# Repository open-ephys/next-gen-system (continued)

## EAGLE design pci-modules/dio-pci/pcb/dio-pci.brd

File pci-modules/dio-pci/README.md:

# Intan & DIO FMC Daughter Card

This board roughly conforms the PCIe card mechanical standard and uses a flex
FMC cable to connect to the master FPGA module. This board performs all
communication over FMC -- the PCIe slot design is for mechanical support and to
provide a common and standardized mounting solution across acquisition PCs

This card is part of the overall proposed architecture of the next-gen system
which is outlined
[here](https://open-ephys.atlassian.net/wiki/display/OEW/PCIe+acquisition+board)

### Features
- See TODO item on isolation...
- 2x isolated intan compatible 12pin omnetics connectors (A & B) for the intan headstage SPI standard, isolated through LVDS to CMOS converters and galvanic isolators. This headstage has its own power supply that is fed through am isolated DC-DC converter.
- 4x directional SMA connectors (on the card front edge) that are routed through the same isolation circuit as headstage connectors

### Pinout
FMC LPC pinout can be found [here](https://docs.google.com/spreadsheets/d/18WfmbLGt8bGUUdksKp6AKA_wMX2SJ3Tndin-nnEgUCs/edit#gid=584734392)

### BOM
The bill of materials for this device can be found
[here](https://docs.google.com/spreadsheets/d/18WfmbLGt8bGUUdksKp6AKA_wMX2SJ3Tndin-nnEgUCs/edit?usp=sharing).

## Manufacturing requirements

TODO:
- PCB thickness:
- 4 layers
- 8mil trace width & spacing
- 12mil min. drill

PCI Brackets:
http://www.mouser.com/Search/ProductDetail.aspx?R=9203virtualkey53400000virtualkey534-9203
http://www.cbttechnology.com/products/s/PCI/PCI-blanks-database.php
http://www.keyelco.com/category.cfm/Standard-Blanks/Computer-Bracket-Blanks-With-Tabs/p/427/id/704/c_id/899

There is one 0.05" pitch BGA connector (the samtech FMC connector) and a few omnetics connectors with inacessible pins on the board, so a stencil and reflow soldering need to be used.

The Samtec FMC connector might need to be clamped or held down during reflow soldering. The samtec docs state that they should settle on their own during reflow though, so trying that first seems like a good idea (  http://suddendocs.samtec.com/processing/searay_soldering1.pdf ).

There is a round pad of kapton tape on the connector to provide a clamping surface for this purpose. We have had good success with using a steel paperclip that we modified to exert less force by cutting two slots into the spring. The original paper clips push down too hard and can warp the conenctor. Possibly just weighting it down with a suitable object could also work. Finally, the size of the connector means that it heats up pretty slowly, so expect it to reflow after everything else on the board, and if possible use proper pre-heating.

In order to meet approximately correct trace impedances, the design further is assuming:
 - 1oz copper
 - ~1.2mm total board height, ~0.25mm per layer, dielectric ER = 4.5

## TODO (Rev 1.0)
- [ ] Instead of conforming to VITA 57, PCB footprint should be made to fit in
  a PC expansion slot and be connected to the KC705 using a flex [FMC
  cable](http://suddendocs.samtec.com/prints/hdr-169472-xx-mkt.pdf). This will
  modularize the IO modules, potentially creating an ecosystem of different
  modules for different applications. It will also use extremely standardized
  interface (rear PC expansion slots) which also have excellent
  electrical/mechanical characteristics.
    - A couple interesting IO Module ideas
        - Analog module (e.g. NI DAQ replacement with some beefy multiplex SAR
          ADC and DAC on it)
        - Isolated Intan module (Similar to existing design, featuring galvanic
          isolation)
        - Adjustable logic level digital IO module
        - SPI compression module
        - Etc...
- [ ] As per [page 24 of the KC705 user
  guide](http://www.xilinx.com/support/documentation/boards_and_kits/kc705/ug810_KC705_Eval_Bd.pdf)
  we need to jumper the TDI and TDO pins of our FMC connectors to allow pass
  through of JTAG signals so the FPGA can be programmed when the FMC module is
  connected.
- [ ] For galvanically isolated IO module, we should conform to human use
  standards. Jakob has some info on what is required for this.
- [ ] SMA input jacks should optionally terminate in 50 Ohms via a transistor switch
- [ ] SMA outputs should have 50 ohm characteristic impedance and use line
  drivers capable of reaching TTL logic levels (>2V) when driving 50 Ohm load
- [ ] What does isolation mean in the context of being inside a computer
  chassis? I have a feeling that it does not mean much because the case of the
  computer is tied to earth. Isolation will probably need to happen outside the
  computer case. Perhaps keeping the digital IO isolation in place is a good
  idea to prevent users from destroying things, but power/ground isolation
  inside the computer is probably mute.

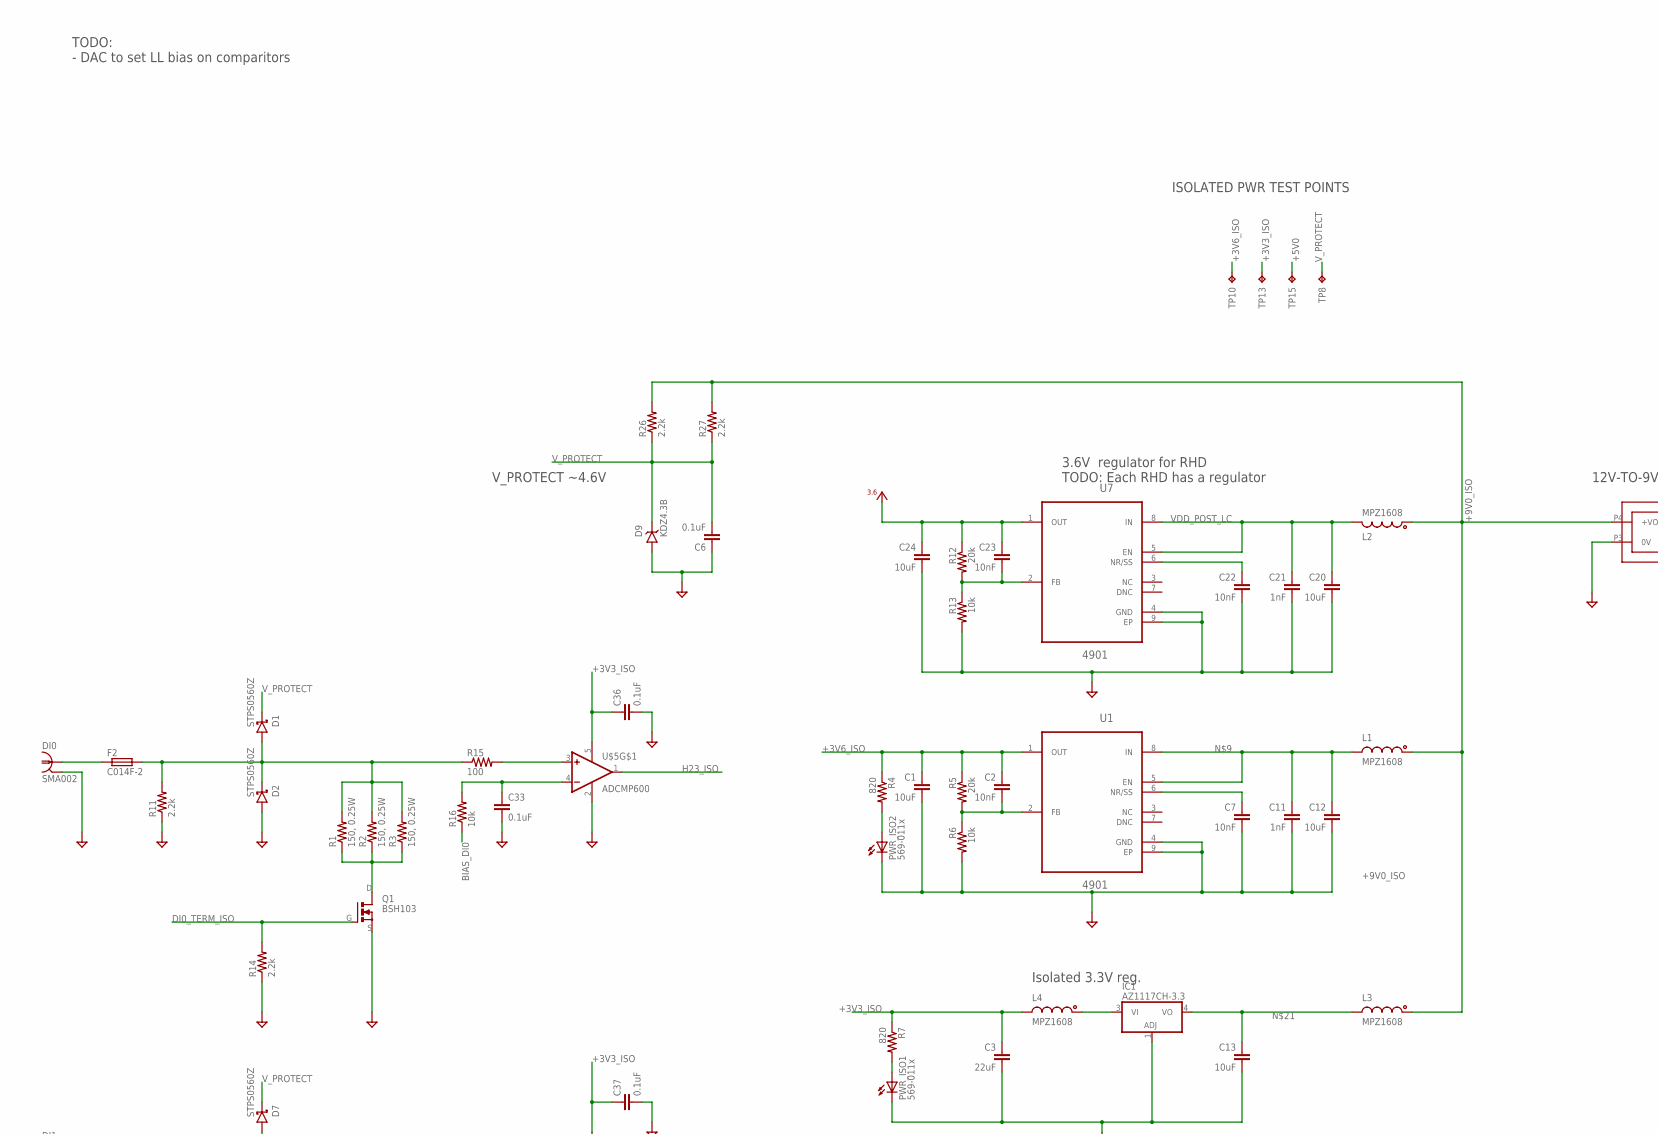
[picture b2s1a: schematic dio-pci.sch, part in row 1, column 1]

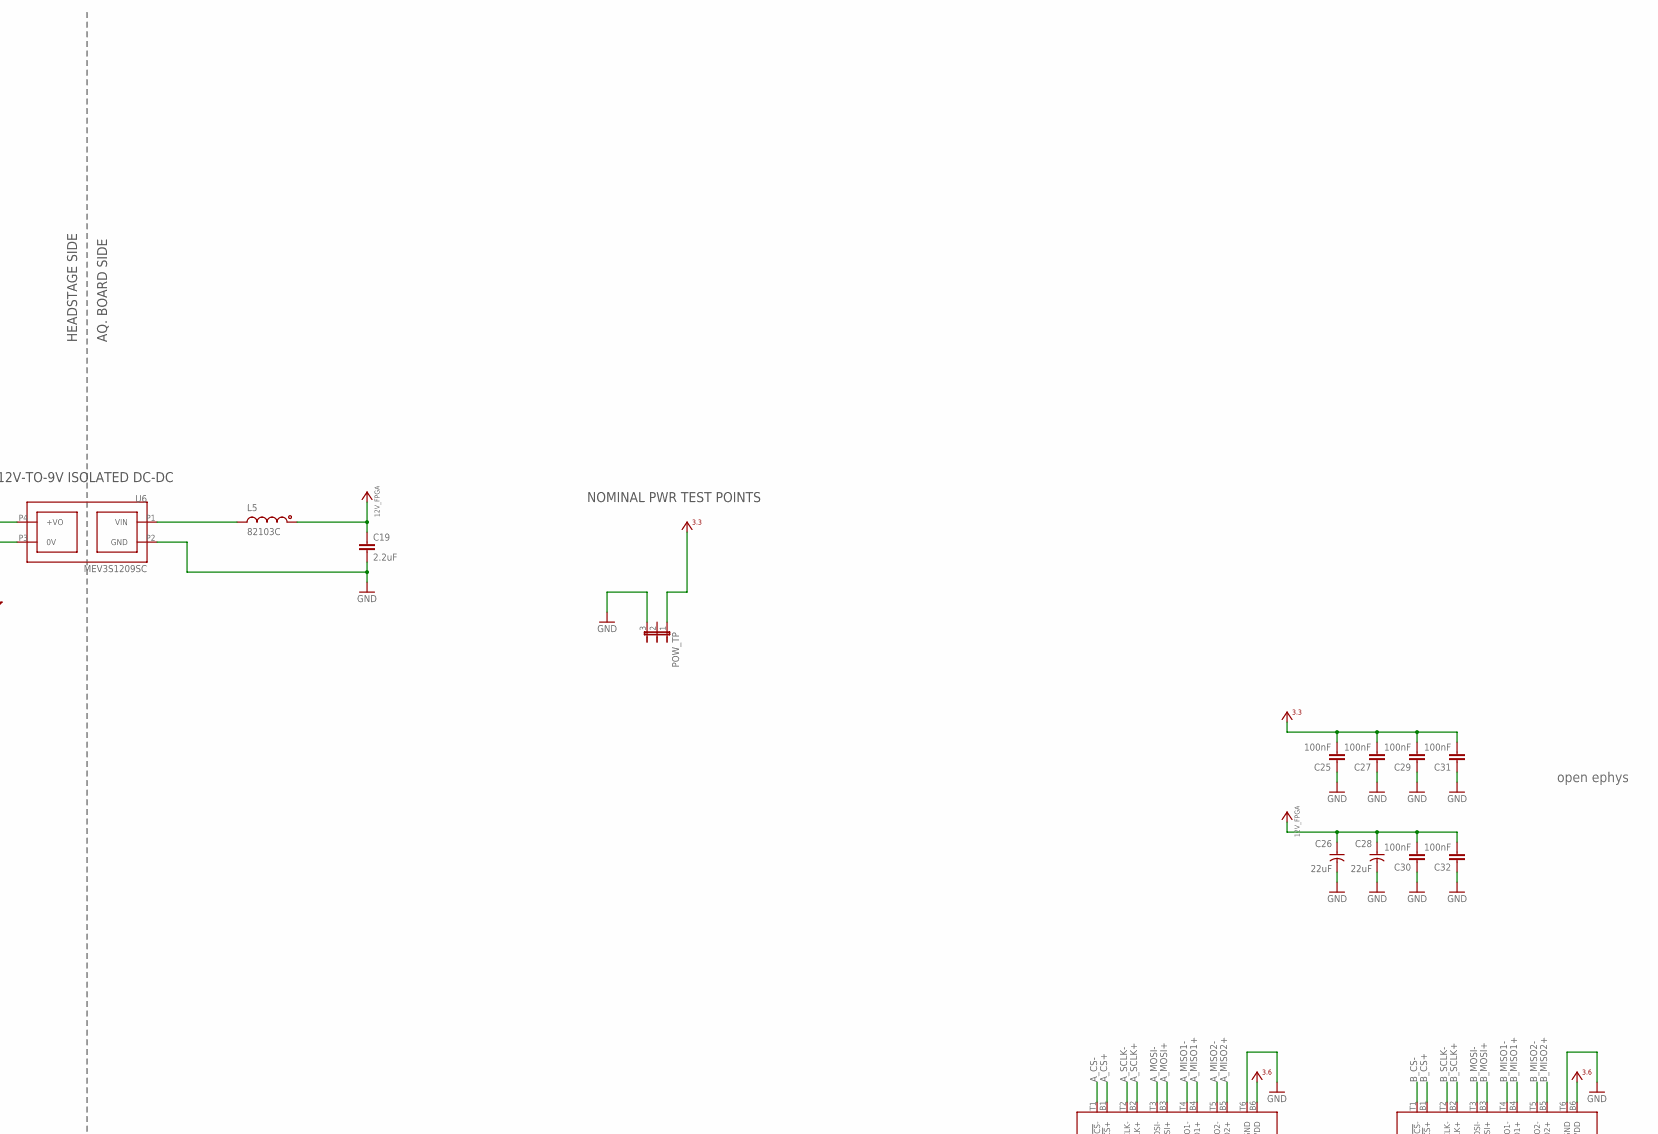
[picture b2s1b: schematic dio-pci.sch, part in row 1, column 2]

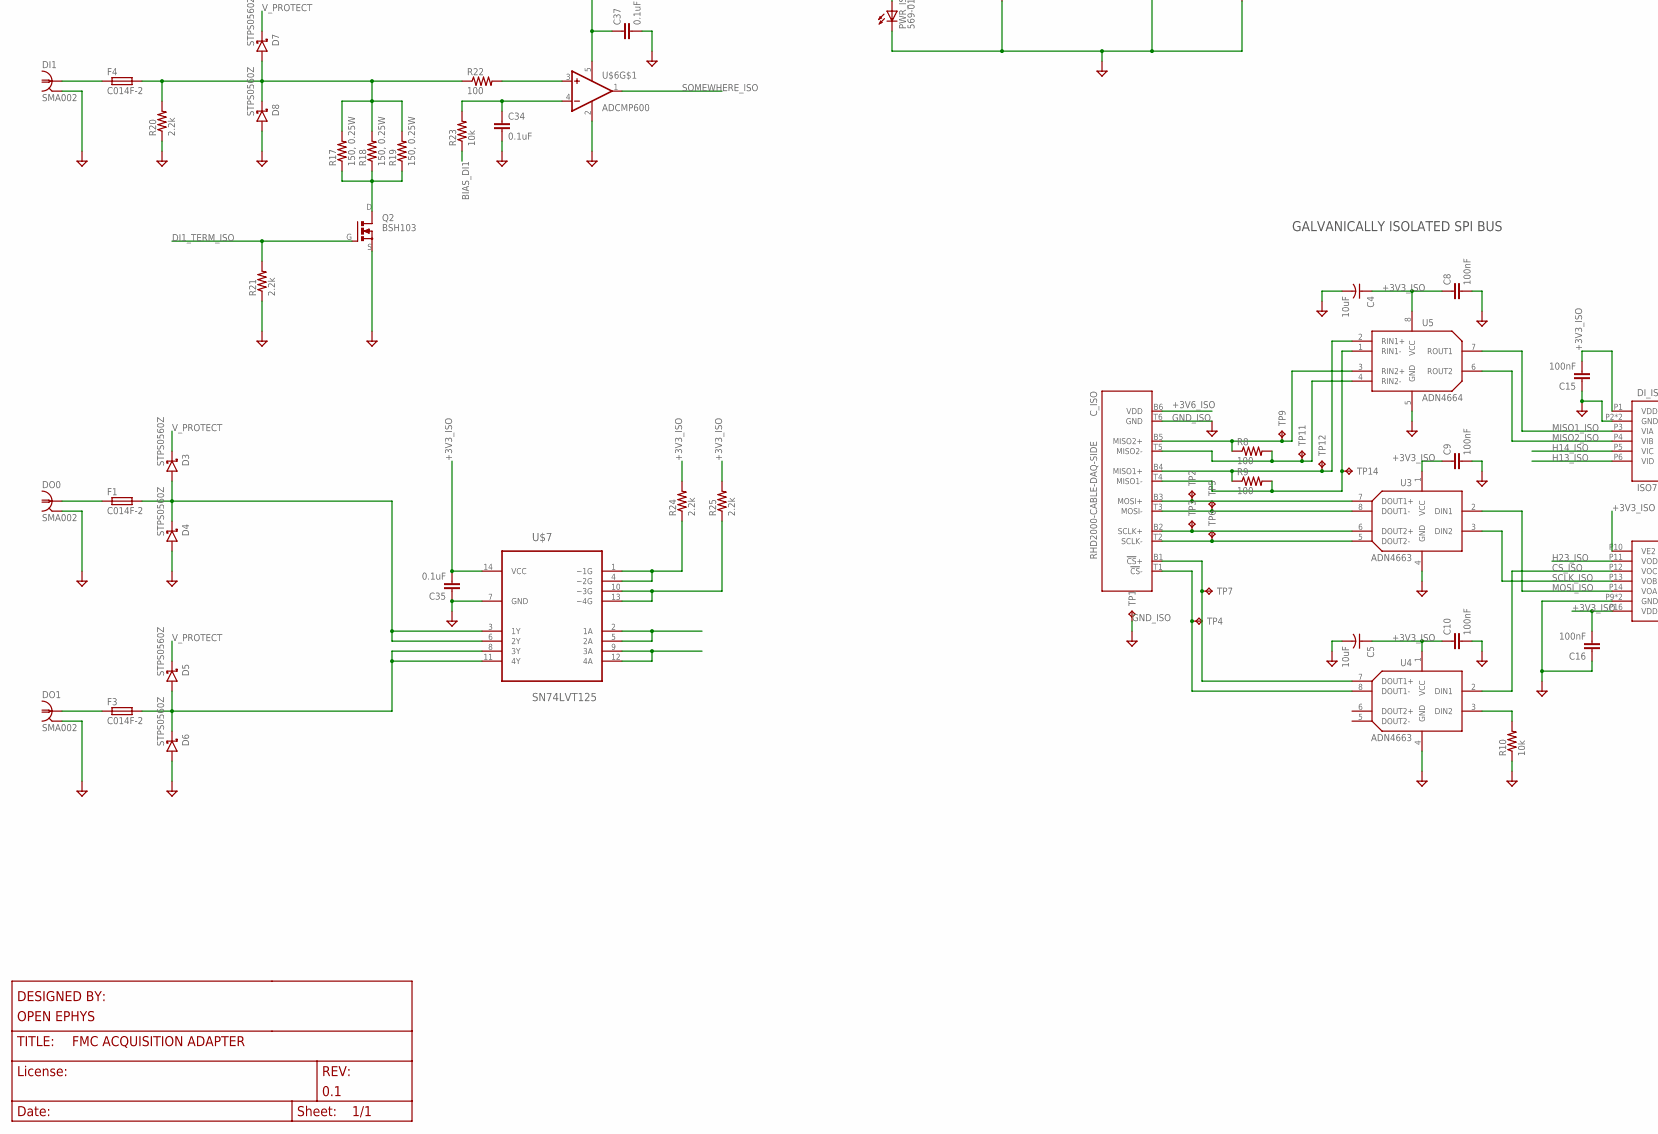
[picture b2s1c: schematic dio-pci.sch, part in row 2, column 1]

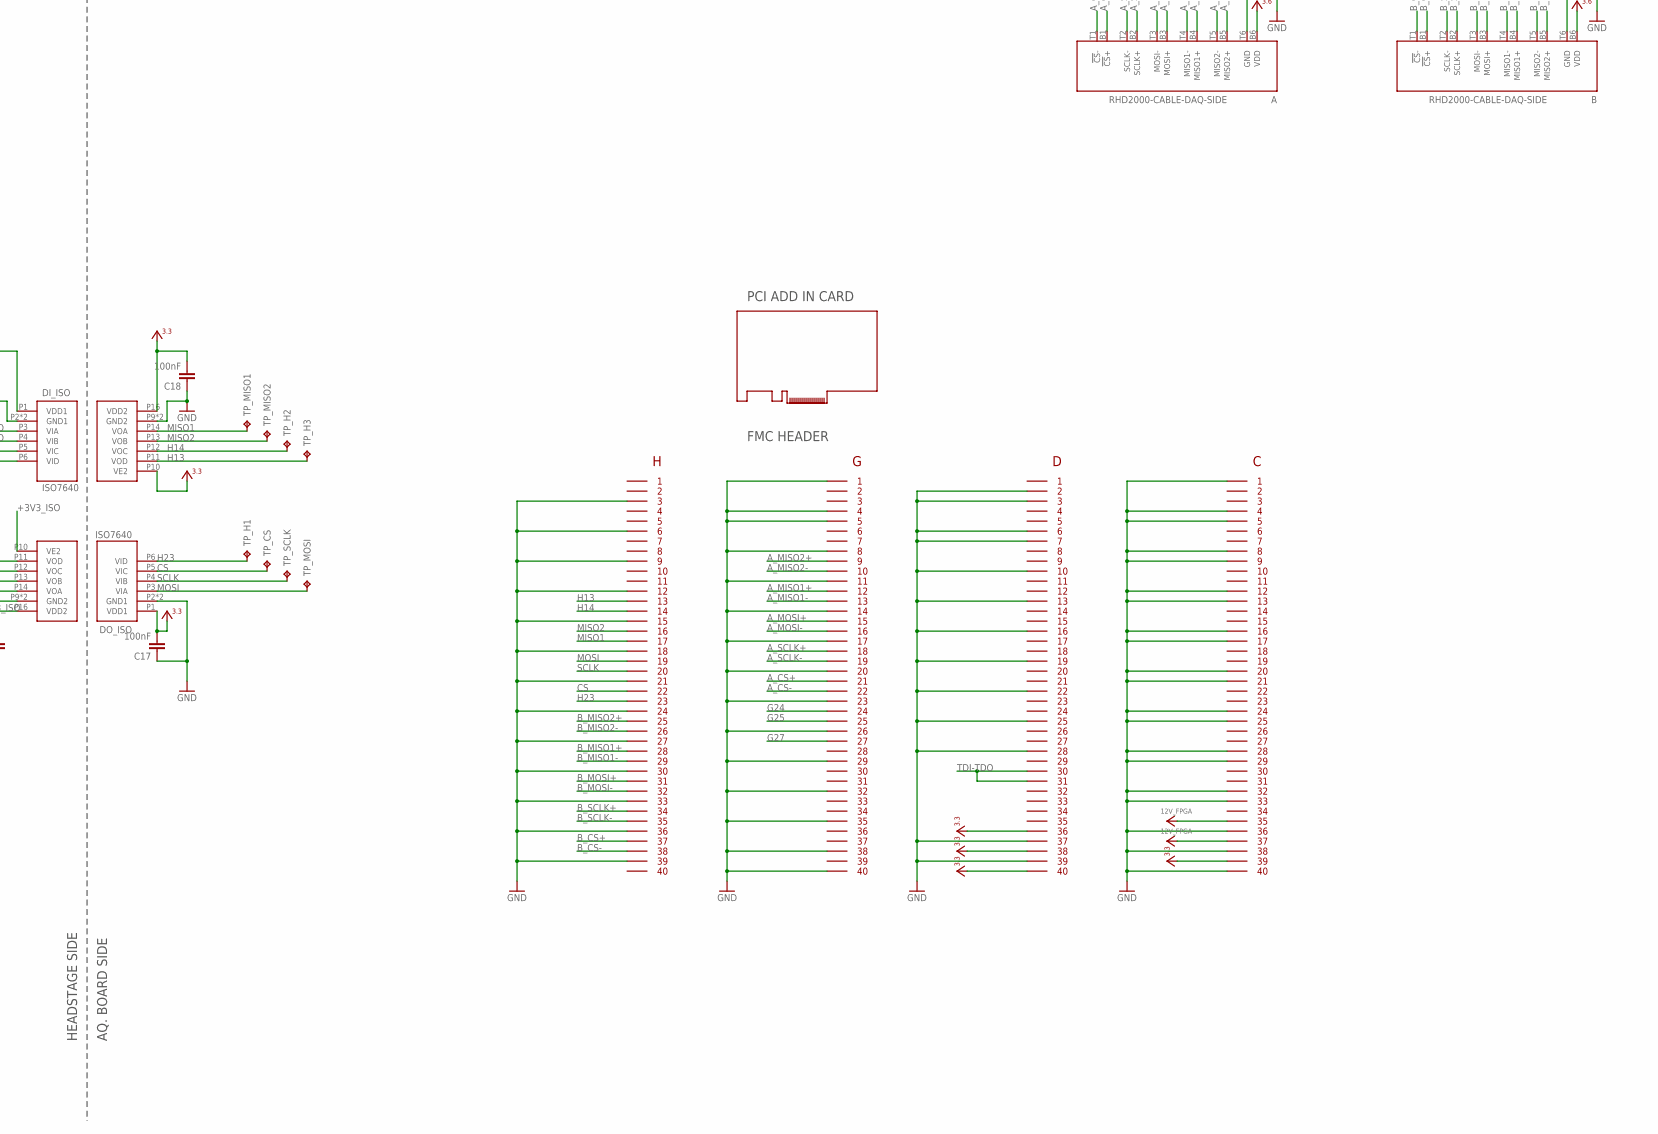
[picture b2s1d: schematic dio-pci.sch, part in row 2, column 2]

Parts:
A: RHD2000-CABLE-DAQ-SIDE; OMNETICS_PZN-12-AA
B: RHD2000-CABLE-DAQ-SIDE; OMNETICS_PZN-12-AA
C1, C12, C13, C20, C24: 10uF; 1206
C2, C7, C22, C23: 10nF; 0603
C3: 22uF; 1206
C4, C5: 10uF; 1206-POL
C6, C33, C34, C35, C36, C37: 0.1uF; 0603
C8, C9, C10, C15, C16, C17, C18, C25, C27, C29, C30, C31, C32: 100nF; 0603
C11, C21: 1nF; 0603
C19: 2.2uF; 1206
C26, C28: 22uF; 1210-POL
C_ISO: RHD2000-CABLE-DAQ-SIDE; OMNETICS_PZN-12-AA
D1, D2, D3, D4, D5, D6, D7, D8: STPS0560Z; SOD123
D9: KDZ4.3B; SOD123
DI0, DI1: SMA002; SMA_JACK_CONREVSMA002-G
DI_ISO: ISO7640; SOIC_WIDE_16
DO0, DO1: SMA002; SMA_JACK_CONREVSMA002-G
DO_ISO: ISO7640; SOIC_WIDE_16
F1, F2, F3, F4: C014F-2; 1812
FMC: FMC_LPC_160_PIN; FMC_LPC_MALE_WITH_SP601_BSILK
IC1: AZ1117CH-3.3; SOT223
L1, L2, L3, L4: MPZ1608; 0603
L5: 82103C; 1210
POW_TP: JP3E; JP3
PWR_ISO: 569-011x; 569-011X-X00_LED_ARRAY
Q1, Q2: BSH103; SOT23-GSD
R1, R2, R3, R17, R18, R19: 150, 0.25W; 1206
R4, R7: 820; 0603
R5, R12: 20k; 0603
R6, R10, R13, R16, R23: 10k; 0603
R8, R9, R15, R22: 100; 0603
R11, R14, R20, R21, R24, R25, R26, R27: 2.2k; 0603
TP1: GND-ISO; P1-13
TP2: MOSI+; TP06R
TP3: SCLK+; TP06R
TP4: CS-; TP06R
TP5: MOSI-; TP06R
TP6: SCLK-; TP06R
TP7: CS+; TP06R
TP8, TP15: +5V0; TP06R
TP9: MISO2+; TP06R
TP10: +3V6; TP06R
TP11: MISO2-; TP06R
TP12: MISO1+; TP06R
TP13: +3V3; TP06R
TP14: MISO1-; TP06R
TP_CS: CS; TP06R
TP_H1: H23; TP06R
TP_H2: H14; TP06R
TP_H3: H13; TP06R
TP_MISO1: MISO1; TP06R
TP_MISO2: MISO2; TP06R
TP_MOSI: MOSI; TP06R
TP_SCLK: SCLK; TP06R
U1, U7: 4901; SOP65P490X110-9N
U3, U4: ADN4663; SOIC127P500X400-8N
U5: ADN4664; SOIC127P500X400-8N
U6: MEV3S1209SC; MEV3
U$1: OPEN_EPHYS_LOGO
U$2: PCI-MECH_STD-H_HALF-W; PCI-ADDIN_STD-H_HALF-L
U$5, U$6: ADCMP600; SOT-23-5
U$7: SN74LVT125; SO14

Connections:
12V_FPGA: C19.1, C26.+, C28.+, C30.2, C32.2, FMC.P$155, FMC.P$157, L5.1
$N1: D7.A, D8.C, F4.2, R17.2, R18.2, R19.2, R20.2, R22.1
$N3: D1.A, D2.C, F2.2, R1.2, R2.2, R3.2, R11.2, R15.1
$N101: D3.A, D4.C, F1.2, U$7.3 (1Y), U$7.6 (2Y)
$N102: D5.A, D6.C, F3.2, U$7.8 (3Y), U$7.11 (4Y)
+3V3: C17.2, C18.2, C25.2, C27.2, C29.2, C31.2, DI_ISO.P10 (VE2), DI_ISO.P16 (VDD2), DO_ISO.P1 (VDD1), FMC.P$116, FMC.P$118, FMC.P$120, FMC.P$159, POW_TP.1
+3V3_ISO: C3.1, C4.+, C5.+, C8.1, C9.1, C10.1, C15.2, C16.2, C35.2, C36.1, C37.1, DI_ISO.P1 (VDD1), DO_ISO.P10 (VE2), DO_ISO.P16 (VDD2), L4.2, R7.1, R24.2, R25.2, TP13.TP, U3.1 (VCC), U4.1 (VCC), U5.8 (VCC), U$5.5 (V+), U$6.5 (V+), U$7.14 (VCC)
+3V6: A.B6 (VDD), B.B6 (VDD), C23.1, C24.1, R12.1, U7.1 (OUT)
+3V6_ISO: C1.1, C2.1, C_ISO.B6 (VDD), R4.1, R5.1, TP10.TP, U1.1 (OUT)
+5V0: TP15.TP
+9V0_ISO: L1.1, L2.1, L3.1, R26.2, R27.2, U6.P4 (+VO)
AGND1: C23.2, R12.2, R13.1, U7.2 (FB)
AGND2: C2.2, R5.2, R6.1, U1.2 (FB)
A_CS+: A.B1 (!CS!+), FMC.P$61
A_CS-: A.T1 (!CS!-), FMC.P$62
A_MISO1+: A.B4 (MISO1+), FMC.P$52
A_MISO1-: A.T4 (MISO1-), FMC.P$53
A_MISO2+: A.B5 (MISO2+), FMC.P$49
A_MISO2-: A.T5 (MISO2-), FMC.P$50
A_MOSI+: A.B3 (MOSI+), FMC.P$55
A_MOSI-: A.T3 (MOSI-), FMC.P$56
A_SCLK+: A.B2 (SCLK+), FMC.P$58
A_SCLK-: A.T2 (SCLK-), FMC.P$59
BIAS_DI0: R16.1
BIAS_DI1: R23.1
B_CS+: B.B1 (!CS!+), FMC.P$37
B_CS-: B.T1 (!CS!-), FMC.P$38
B_MISO1+: B.B4 (MISO1+), FMC.P$28
B_MISO1-: B.T4 (MISO1-), FMC.P$29
B_MISO2+: B.B5 (MISO2+), FMC.P$25
B_MISO2-: B.T5 (MISO2-), FMC.P$26
B_MOSI+: B.B3 (MOSI+), FMC.P$31
B_MOSI-: B.T3 (MOSI-), FMC.P$32
B_SCLK+: B.B2 (SCLK+), FMC.P$34
B_SCLK-: B.T2 (SCLK-), FMC.P$35
CS: DO_ISO.P5 (VIC), FMC.P$22, TP_CS.TP
CS+_ISOLATED: C_ISO.B1 (!CS!+), TP7.TP, U4.7 (DOUT1+)
CS-_ISOLATED: C_ISO.T1 (!CS!-), TP4.TP, U4.8 (DOUT1-)
CS_ISO: DO_ISO.P12 (VOC), U4.2 (DIN1)
DI0_TERM_ISO: Q1.G, R14.2
DI1_TERM_ISO: Q2.G, R21.2
G24: FMC.P$64
G25: FMC.P$65
G27: FMC.P$67
GND: A.T6 (GND), B.T6 (GND), C17.1, C18.1, C19.2, C25.1, C26.-, C27.1, C28.-, C29.1, C30.1, C31.1, C32.1, DI_ISO.P9 (GND2), DI_ISO.P15 (GND2), DO_ISO.P2 (GND1), DO_ISO.P8 (GND1), FMC.GNDA (GND), FMC.GNDB (GND), FMC.P$3, FMC.P$6, FMC.P$9, FMC.P$12, FMC.P$15, FMC.P$18, FMC.P$21, FMC.P$24, FMC.P$27, FMC.P$30, FMC.P$33, FMC.P$36, FMC.P$39, FMC.P$41, FMC.P$44, FMC.P$45, FMC.P$48, FMC.P$51, FMC.P$54, FMC.P$57, FMC.P$60, FMC.P$63, FMC.P$66, FMC.P$69, FMC.P$72, FMC.P$75, FMC.P$78, FMC.P$80, FMC.P$82, FMC.P$83, FMC.P$86, FMC.P$87, FMC.P$90, FMC.P$93, FMC.P$96, FMC.P$99, FMC.P$102, FMC.P$105, FMC.P$108, FMC.P$117, FMC.P$119, FMC.P$121, FMC.P$124, FMC.P$125, FMC.P$128, FMC.P$129, FMC.P$132, FMC.P$133, FMC.P$136, FMC.P$137, FMC.P$140, FMC.P$141, FMC.P$144, FMC.P$145, FMC.P$148, FMC.P$149, FMC.P$152, FMC.P$153, FMC.P$156, FMC.P$158, FMC.P$160, POW_TP.3, U6.P2 (GND)
GND_ISO: C1.2, C3.2, C4.-, C5.-, C6.1, C7.2, C8.2, C9.2, C10.2, C11.2, C12.2, C13.2, C15.1, C16.1, C20.2, C21.2, C22.2, C24.2, C33.2, C34.2, C35.1, C36.2, C37.2, C_ISO.T6 (GND), D2.A, D4.A, D6.A, D8.A, D9.A, DI0.GND$1 (2), DI0.GND$2 (2), DI0.GND$3 (2), DI0.GND$4 (2), DI1.GND$1 (2), DI1.GND$2 (2), DI1.GND$3 (2), DI1.GND$4 (2), DI_ISO.P2 (GND1), DI_ISO.P8 (GND1), DO0.GND$1 (2), DO0.GND$2 (2), DO0.GND$3 (2), DO0.GND$4 (2), DO1.GND$1 (2), DO1.GND$2 (2), DO1.GND$3 (2), DO1.GND$4 (2), DO_ISO.P9 (GND2), DO_ISO.P15 (GND2), IC1.1 (ADJ), PWR_ISO.C1 (C), PWR_ISO.C2 (C), Q1.S, Q2.S, R6.2, R10.1, R11.1, R13.2, R14.1, R20.1, R21.1, TP1.TP, U1.4 (GND), U1.9 (EP), U3.4 (GND), U4.4 (GND), U5.5 (GND), U6.P3 (0V), U7.4 (GND), U7.9 (EP), U$5.2 (V-), U$6.2 (V-), U$7.7 (GND)
H13: DI_ISO.P11 (VOD), FMC.P$13, TP_H3.TP
H13_ISO: DI_ISO.P6 (VID), U$7.9 (3A), U$7.12 (4A)
H14: DI_ISO.P12 (VOC), FMC.P$14, TP_H2.TP
H14_ISO: DI_ISO.P5 (VIC), U$7.2 (1A), U$7.5 (2A)
H23: DO_ISO.P6 (VID), FMC.P$23, TP_H1.TP
H23_ISO: DO_ISO.P11 (VOD), U$5.1 (OUT)
MISO1: DI_ISO.P14 (VOA), FMC.P$17, TP_MISO1.TP
MISO1+_ISOLATED: C_ISO.B4 (MISO1+), R9.1, TP12.TP, U5.2 (RIN1+)
MISO1-_ISOLATED: C_ISO.T4 (MISO1-), R9.2, TP14.TP, U5.1 (RIN1-)
MISO1_ISO: DI_ISO.P3 (VIA), U5.7 (ROUT1)
MISO2: DI_ISO.P13 (VOB), FMC.P$16, TP_MISO2.TP
MISO2+_ISOLATED: C_ISO.B5 (MISO2+), R8.1, TP9.TP, U5.3 (RIN2+)
MISO2-_ISOLATED: C_ISO.T5 (MISO2-), R8.2, TP11.TP, U5.4 (RIN2-)
MISO2_ISO: DI_ISO.P4 (VIB), U5.6 (ROUT2)
MOSI: DO_ISO.P3 (VIA), FMC.P$19, TP_MOSI.TP
MOSI_ISO: DO_ISO.P14 (VOA), U3.2 (DIN1)
unnamed: C22.1, U7.6 (NR/SS)
unnamed: Q1.D, R1.1, R2.1, R3.1
unnamed: R15.2, U$5.3 (+IN)
unnamed: C7.1, U1.6 (NR/SS)
unnamed: R10.2, U4.3 (DIN2)
unnamed: DI1.CLK (1), F4.1
unnamed: Q2.D, R17.1, R18.1, R19.1
unnamed: PWR_ISO.A2 (A), R4.2
unnamed: C11.1, C12.1, L1.2, U1.5 (EN), U1.8 (IN)
unnamed: PWR_ISO.A1 (A), R7.2
unnamed: DI0.CLK (1), F2.1
unnamed: C_ISO.B3 (MOSI+), TP2.TP, U3.7 (DOUT1+)
unnamed: C_ISO.T3 (MOSI-), TP5.TP, U3.8 (DOUT1-)
unnamed: DO0.CLK (1), F1.1
unnamed: C_ISO.B2 (SCLK+), TP3.TP, U3.6 (DOUT2+)
unnamed: C_ISO.T2 (SCLK-), TP6.TP, U3.5 (DOUT2-)
unnamed: DO1.CLK (1), F3.1
unnamed: C33.1, R16.2, U$5.4 (-IN)
unnamed: R22.2, U$6.3 (+IN)
unnamed: C34.1, R23.2, U$6.4 (-IN)
unnamed: C13.1, IC1.4 (VO), L3.2
unnamed: IC1.3 (VI), L4.1
unnamed: L5.2, U6.P1 (VIN)
unnamed: R24.1, U$7.1 (~1G), U$7.4 (~2G)
unnamed: R25.1, U$7.10 (~3G), U$7.13 (~4G)
SCLK: DO_ISO.P4 (VIB), FMC.P$20, TP_SCLK.TP
SCLK_ISO: DO_ISO.P13 (VOB), U3.3 (DIN2)
SOMEWHERE_ISO: U$6.1 (OUT)
TDI-TDO: FMC.P$110, FMC.P$111
VDD_POST_LC: C20.1, C21.1, L2.2, U7.5 (EN), U7.8 (IN)
V_PROTECT: C6.2, D1.C, D3.C, D5.C, D7.C, D9.C, R26.1, R27.1, TP8.TP

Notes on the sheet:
HEADSTAGE SIDE
AQ. BOARD SIDE
Isolated 3.3V reg.
3.6V regulator for RHD TODO: Each RHD has a regulator
12V-TO-9V ISOLATED DC-DC
ISOLATED PWR TEST POINTS
NOMINAL PWR TEST POINTS
GALVANICALLY ISOLATED SPI BUS
FMC HEADER
PCI ADD IN CARD
TODO: - DAC to set LL bias on comparitors
V_PROTECT ~4.6V

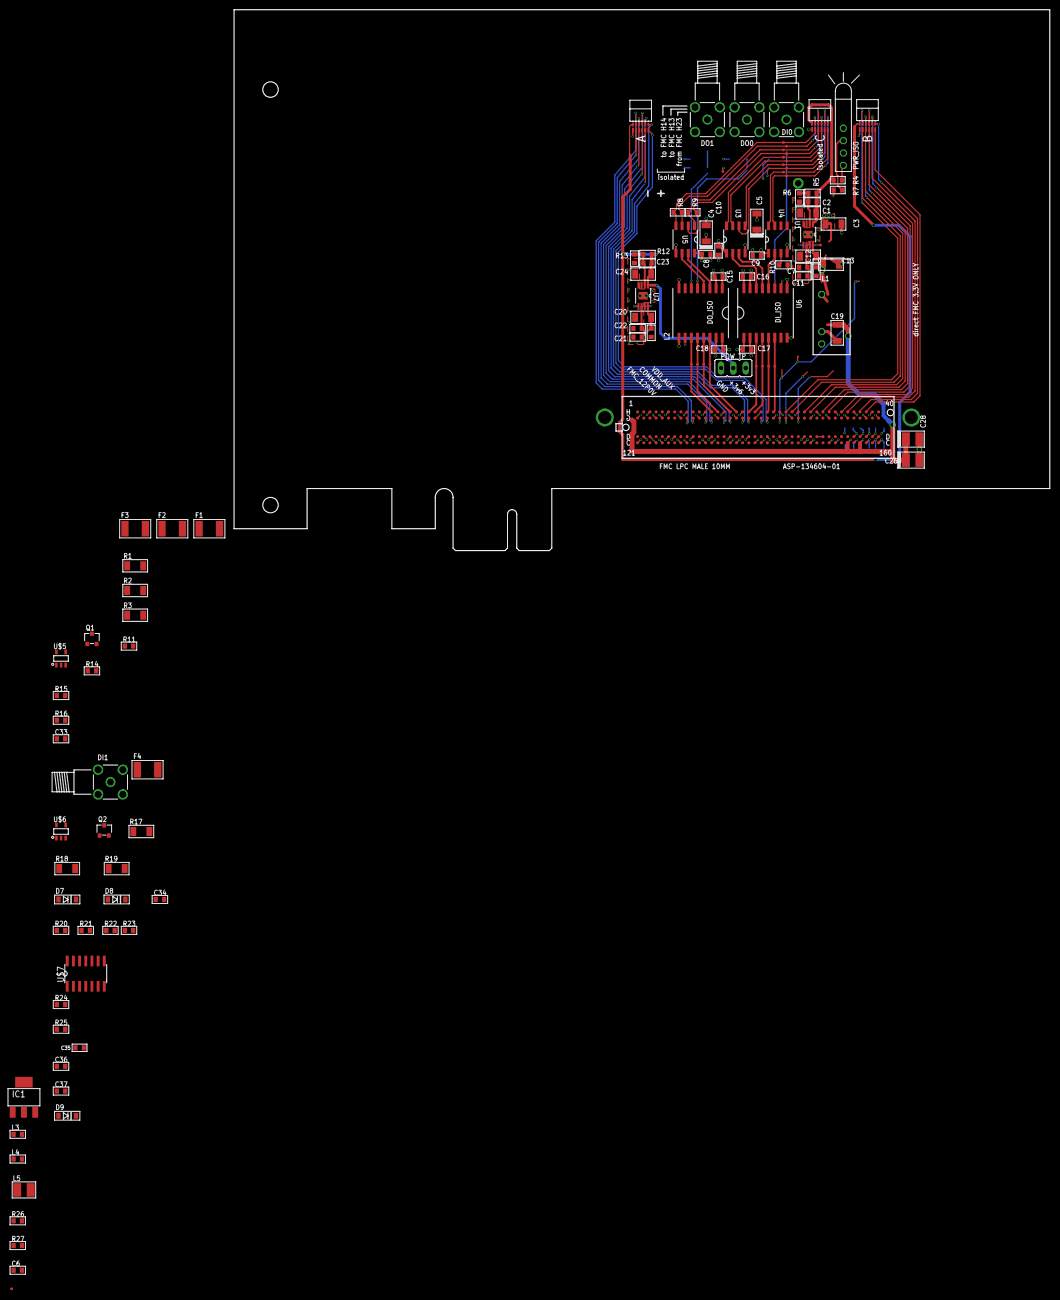
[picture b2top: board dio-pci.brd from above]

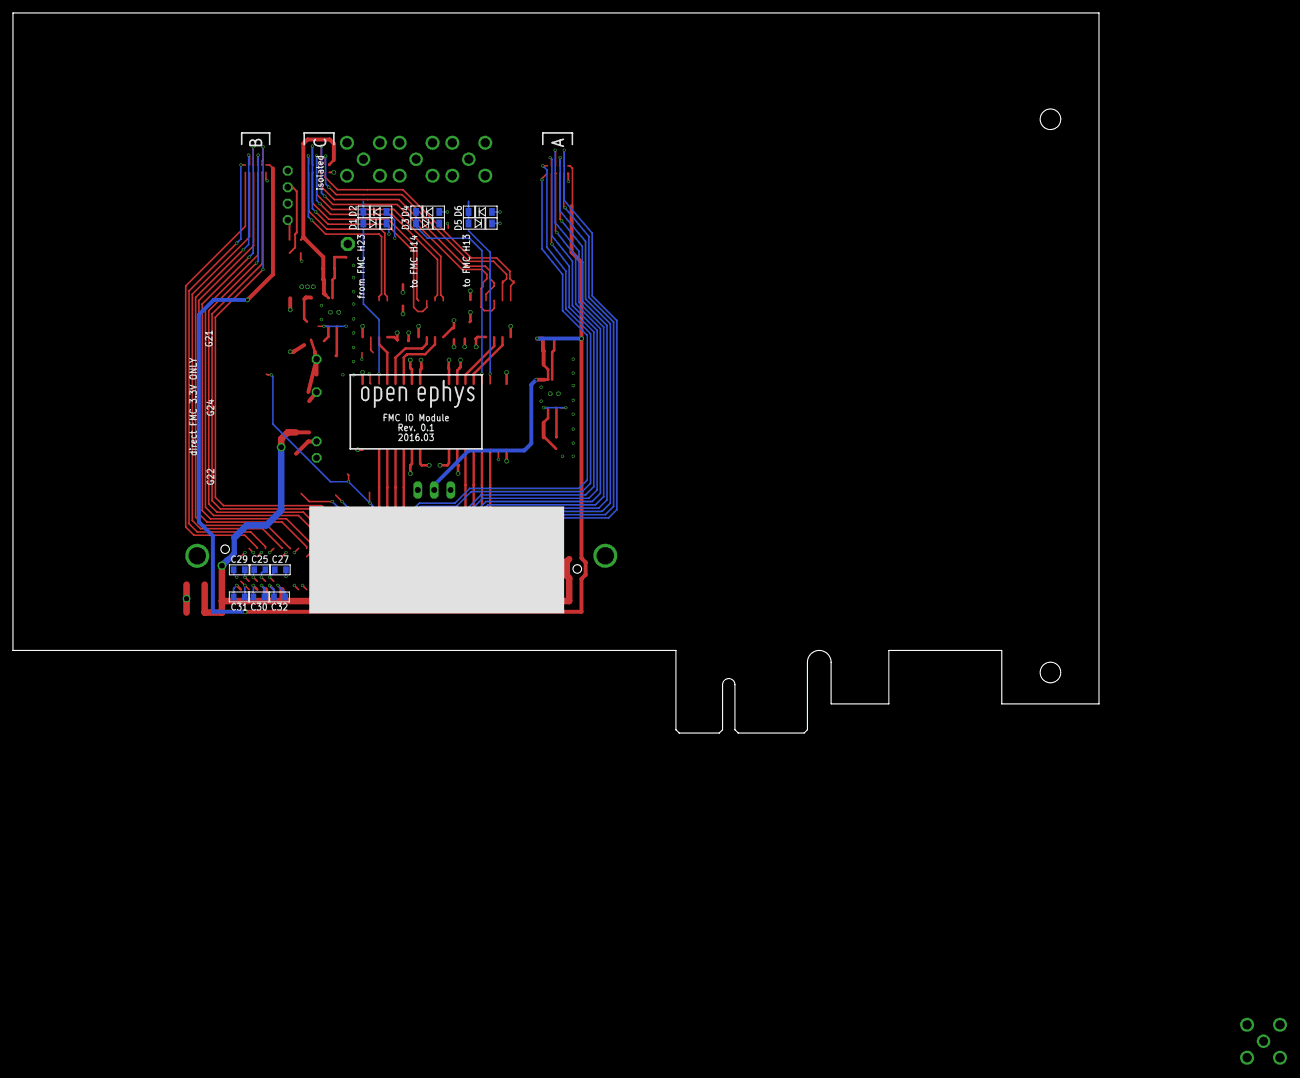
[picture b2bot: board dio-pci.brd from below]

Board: 4 copper layers, 167.6 x 111.2 mm, 130 parts (14 on the bottom side), 86 nets.
